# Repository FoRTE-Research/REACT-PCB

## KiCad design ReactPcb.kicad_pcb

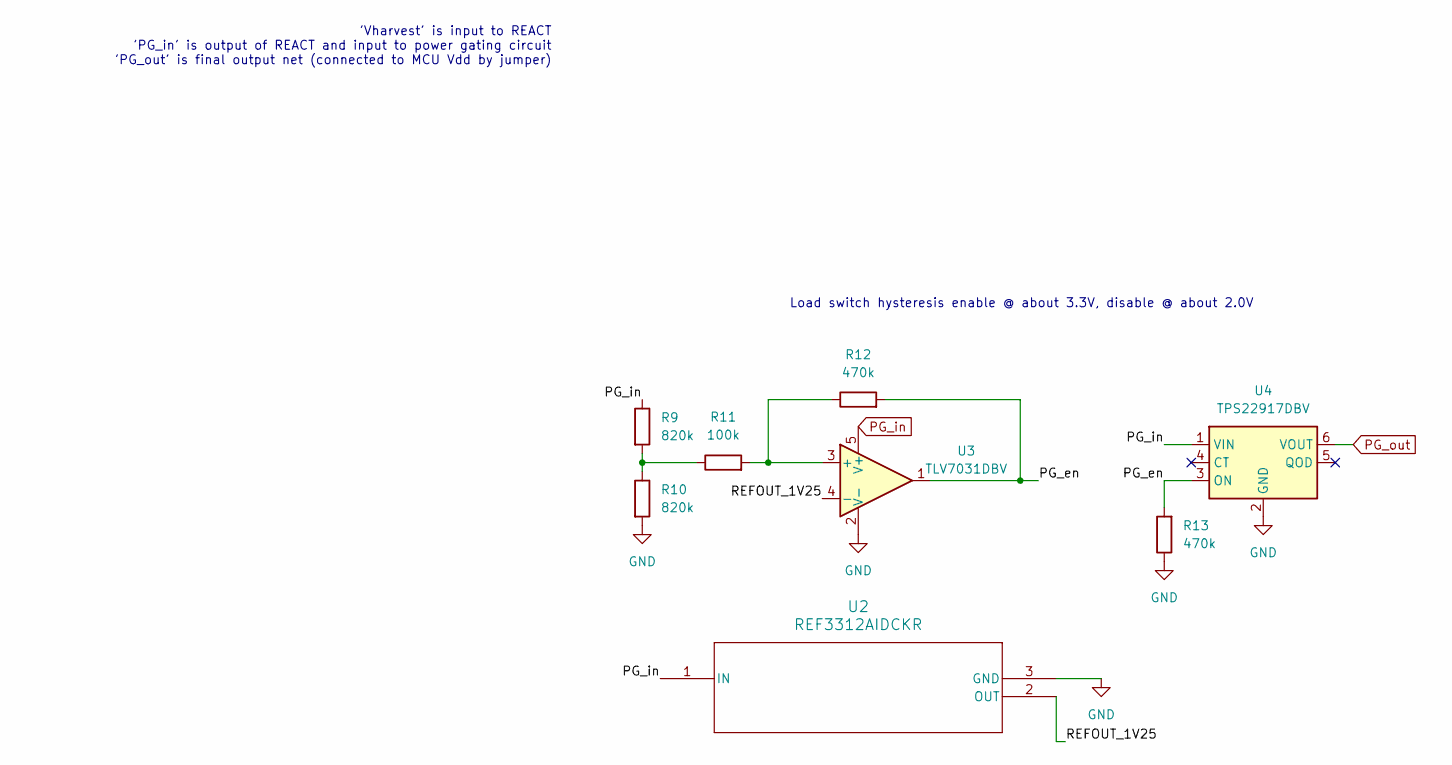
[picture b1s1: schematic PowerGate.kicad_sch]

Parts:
R9, R10: 820k; R_1206_3216Metric
R11: 100k; R_1206_3216Metric
R12, R13: 470k; R_1206_3216Metric
U2: REF3312AIDCKR; DCK3
U3: TLV7031DBV; SOT-23-5
U4: TPS22917DBV; SOT-23-6

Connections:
/Power Gate/PG_en: R12.2, R13.2, U3.1, U4.3 (ON)
/Power Gate/PG_in: R9.1, U2.1 (IN), U3.5 (V+), U4.1 (VIN)
/Power Gate/PG_out: U4.6 (VOUT)
/Power Gate/REFOUT_1V25: U2.2 (OUT), U3.4 (-)
GND: R10.2, R13.1, U2.3 (GND), U3.2 (V-), U4.2 (GND); also elsewhere on the board
unnamed: R9.2, R10.1, R11.1
unnamed: R11.2, R12.1, U3.3 (+)

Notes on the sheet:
'Vharvest' is input to REACT 'PG_in' is output of REACT and input to power gating circuit 'PG_out' is final output net (connected to MCU Vdd by jumper)
Load switch hysteresis enable @ about 3.3V, disable @ about 2.0V

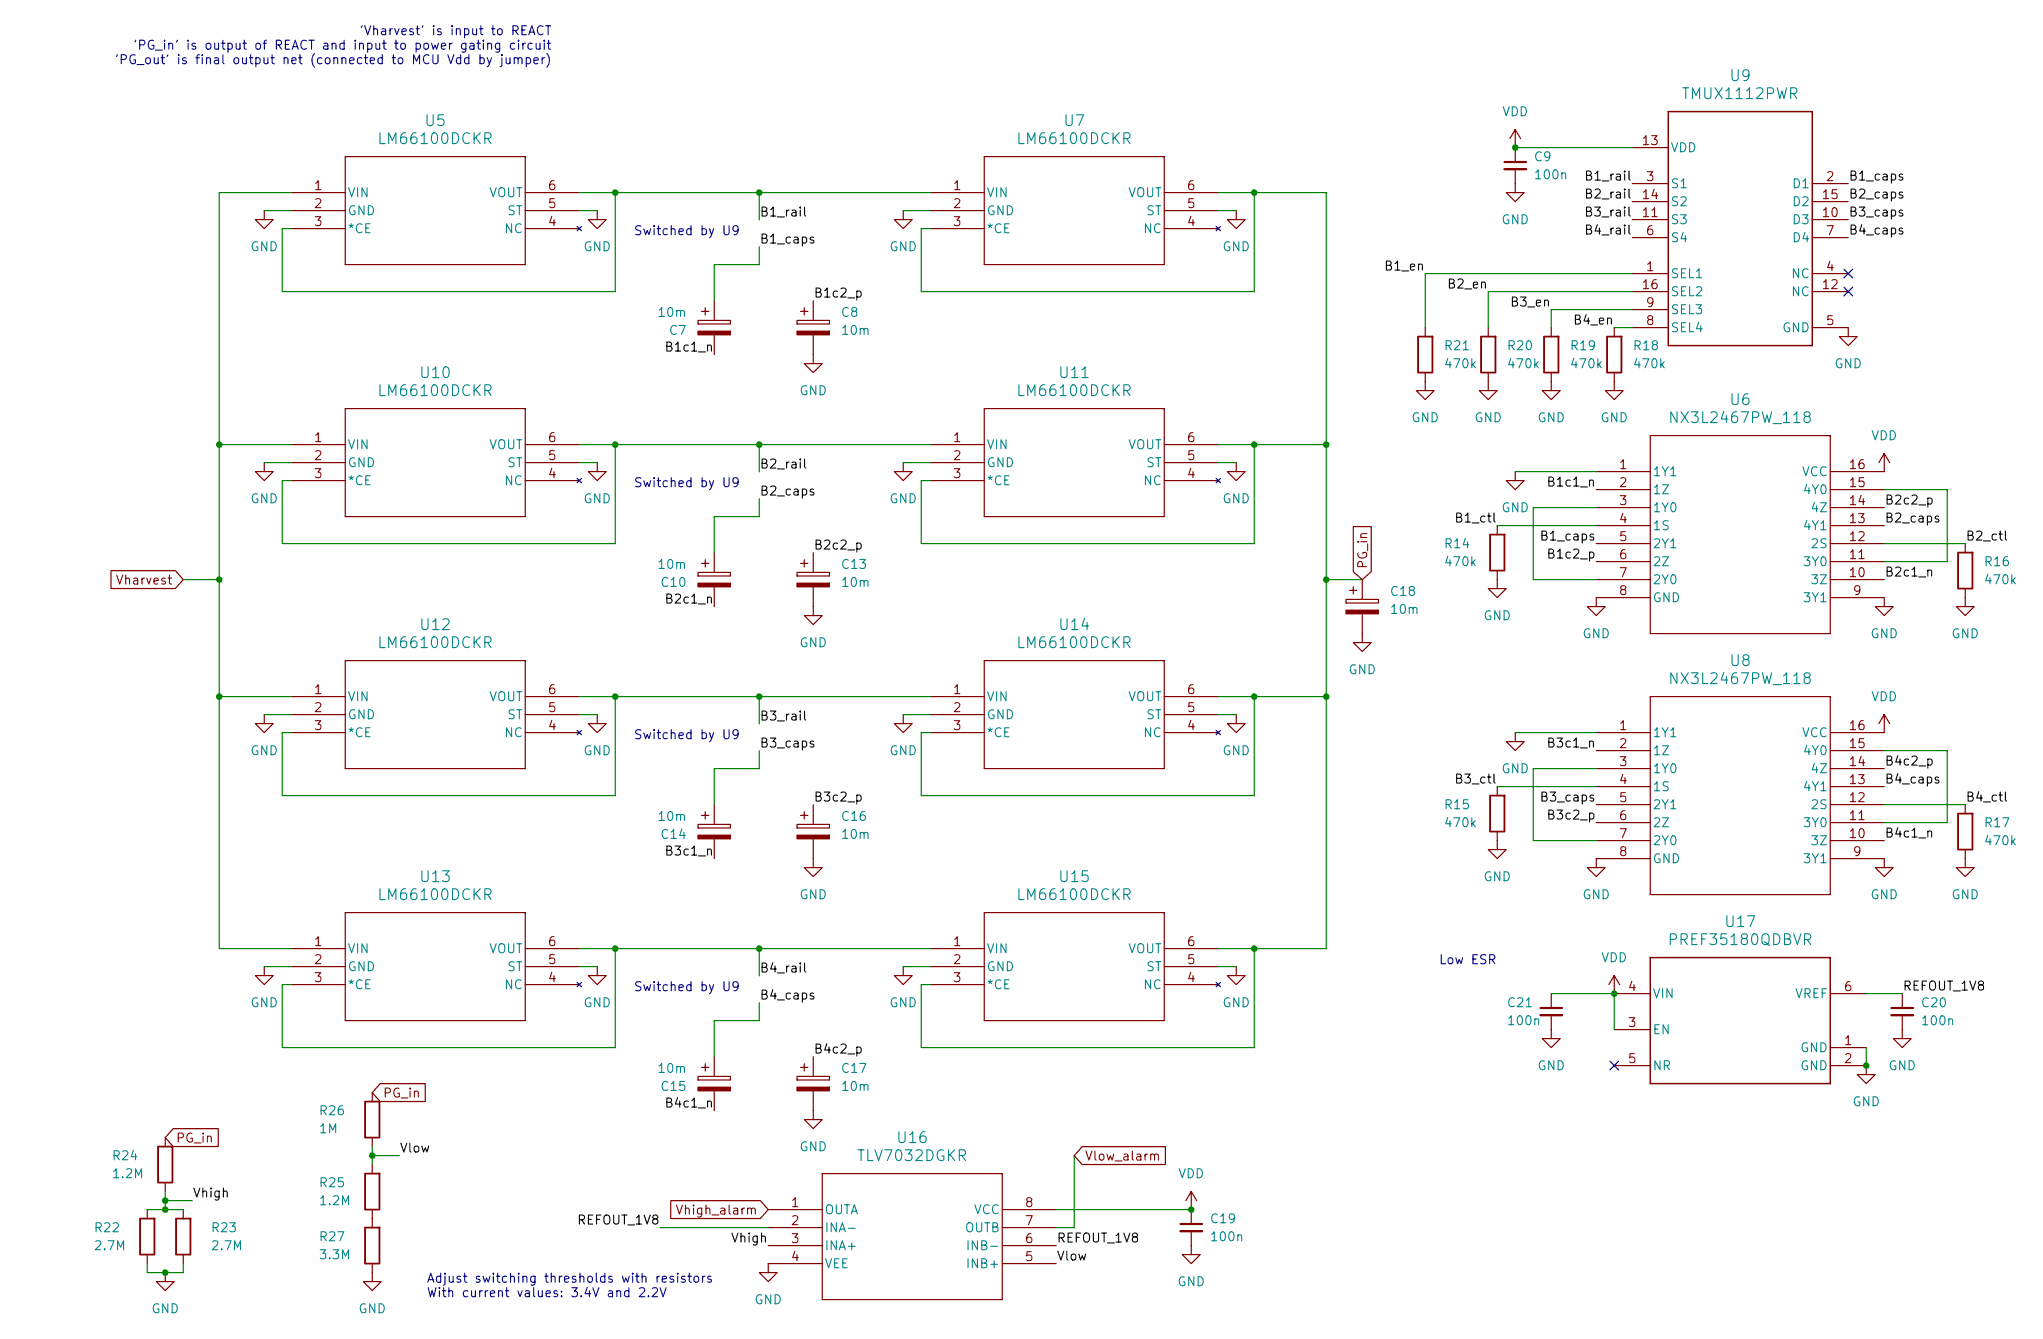
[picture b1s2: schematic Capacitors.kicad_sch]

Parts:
C7, C8, C10, C13, C14, C15, C16, C17, C18: 10m; C_Rect_L10.0mm_W5.0mm_P5.00mm_P7.50mm
C9, C19, C20, C21: 100n; C_1206_3216Metric
R14, R15, R16, R17, R18, R19, R20, R21: 470k; R_1206_3216Metric
R22, R23: 2.7M; R_1206_3216Metric
R24, R25: 1.2M; R_1206_3216Metric
R26: 1M; R_1206_3216Metric
R27: 3.3M; R_1206_3216Metric
U5, U7, U10, U11, U12, U13, U14, U15: LM66100DCKR; DCK6_TEX
U6, U8: NX3L2467PW_118; TSSOP16_SOT403-1_NXP
U9: TMUX1112PWR; PW0016A-IPC_A
U16: TLV7032DGKR; SOIC_32DGKR_TEX
U17: PREF35180QDBVR; DBV0006A-IPC_A

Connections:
/Capacitors/B1_caps: C7.1, U6.5 (2Y1), U9.2 (D1)
/Capacitors/B1_ctl: R14.2, U6.4 (1S)
/Capacitors/B1_en: R21.2, U9.1 (SEL1)
/Capacitors/B1_rail: U5.3 (*CE), U5.6 (VOUT), U7.1 (VIN), U9.3 (S1)
/Capacitors/B1c1_n: C7.2, U6.2 (1Z)
/Capacitors/B1c2_p: C8.1, U6.6 (2Z)
/Capacitors/B2_caps: C10.1, U6.13 (4Y1), U9.15 (D2)
/Capacitors/B2_ctl: R16.2, U6.12 (2S)
/Capacitors/B2_en: R20.2, U9.16 (SEL2)
/Capacitors/B2_rail: U9.14 (S2), U10.3 (*CE), U10.6 (VOUT), U11.1 (VIN)
/Capacitors/B2c1_n: C10.2, U6.10 (3Z)
/Capacitors/B2c2_p: C13.1, U6.14 (4Z)
/Capacitors/B3_caps: C14.1, U8.5 (2Y1), U9.10 (D3)
/Capacitors/B3_ctl: R15.2, U8.4 (1S)
/Capacitors/B3_en: R19.2, U9.9 (SEL3)
/Capacitors/B3_rail: U9.11 (S3), U12.3 (*CE), U12.6 (VOUT), U14.1 (VIN)
/Capacitors/B3c1_n: C14.2, U8.2 (1Z)
/Capacitors/B3c2_p: C16.1, U8.6 (2Z)
/Capacitors/B4_caps: C15.1, U8.13 (4Y1), U9.7 (D4)
/Capacitors/B4_ctl: R17.2, U8.12 (2S)
/Capacitors/B4_en: R18.2, U9.8 (SEL4)
/Capacitors/B4_rail: U9.6 (S4), U13.3 (*CE), U13.6 (VOUT), U15.1 (VIN)
/Capacitors/B4c1_n: C15.2, U8.10 (3Z)
/Capacitors/B4c2_p: C17.1, U8.14 (4Z)
/Capacitors/Pg_in: C18.1, R24.2, R26.2, U7.3 (*CE), U7.6 (VOUT), U11.3 (*CE), U11.6 (VOUT), U14.3 (*CE), U14.6 (VOUT), U15.3 (*CE), U15.6 (VOUT)
/Capacitors/REFOUT_1V8: C20.1, U16.2 (INA-), U16.6 (INB-), U17.6 (VREF)
/Capacitors/Vhigh: R22.2, R23.2, R24.1, U16.3 (INA+)
/Capacitors/Vhigh_alarm: U16.1 (OUTA)
/Capacitors/Vlow: R25.2, R26.1, U16.5 (INB+)
/Capacitors/Vlow_alarm: U16.7 (OUTB)
GND: C8.2, C9.2, C13.2, C16.2, C17.2, C18.2, C19.2, C20.2, C21.2, R14.1, R15.1, R16.1, R17.1, R18.1, R19.1, R20.1, R21.1, R22.1, R23.1, R27.1, U5.2 (GND), U5.5 (ST), U6.1 (1Y1), U6.8 (GND), U6.9 (3Y1), U7.2 (GND), U7.5 (ST), U8.1 (1Y1), U8.8 (GND), U8.9 (3Y1), U9.5 (GND), U10.2 (GND), U10.5 (ST), U11.2 (GND), U11.5 (ST), U12.2 (GND), U12.5 (ST), U13.2 (GND), U13.5 (ST), U14.2 (GND), U14.5 (ST), U15.2 (GND), U15.5 (ST), U16.4 (VEE), U17.1 (GND), U17.2 (GND); also elsewhere on the board
unnamed: R25.1, R27.2
unnamed: U6.3 (1Y0), U6.7 (2Y0)
unnamed: U6.11 (3Y0), U6.15 (4Y0)
unnamed: U8.3 (1Y0), U8.7 (2Y0)
unnamed: U8.11 (3Y0), U8.15 (4Y0)
VDD: C9.1, C19.1, C21.1, U6.16 (VCC), U8.16 (VCC), U9.13 (VDD), U16.8 (VCC), U17.3 (EN), U17.4 (VIN); also elsewhere on the board
Vharvest: U5.1 (VIN), U10.1 (VIN), U12.1 (VIN), U13.1 (VIN); also elsewhere on the board

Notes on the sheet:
Switched by U9
'Vharvest' is input to REACT 'PG_in' is output of REACT and input to power gating circuit 'PG_out' is final output net (connected to MCU Vdd by jumper)
Low ESR
Adjust switching thresholds with resistors With current values: 3.4V and 2.2V

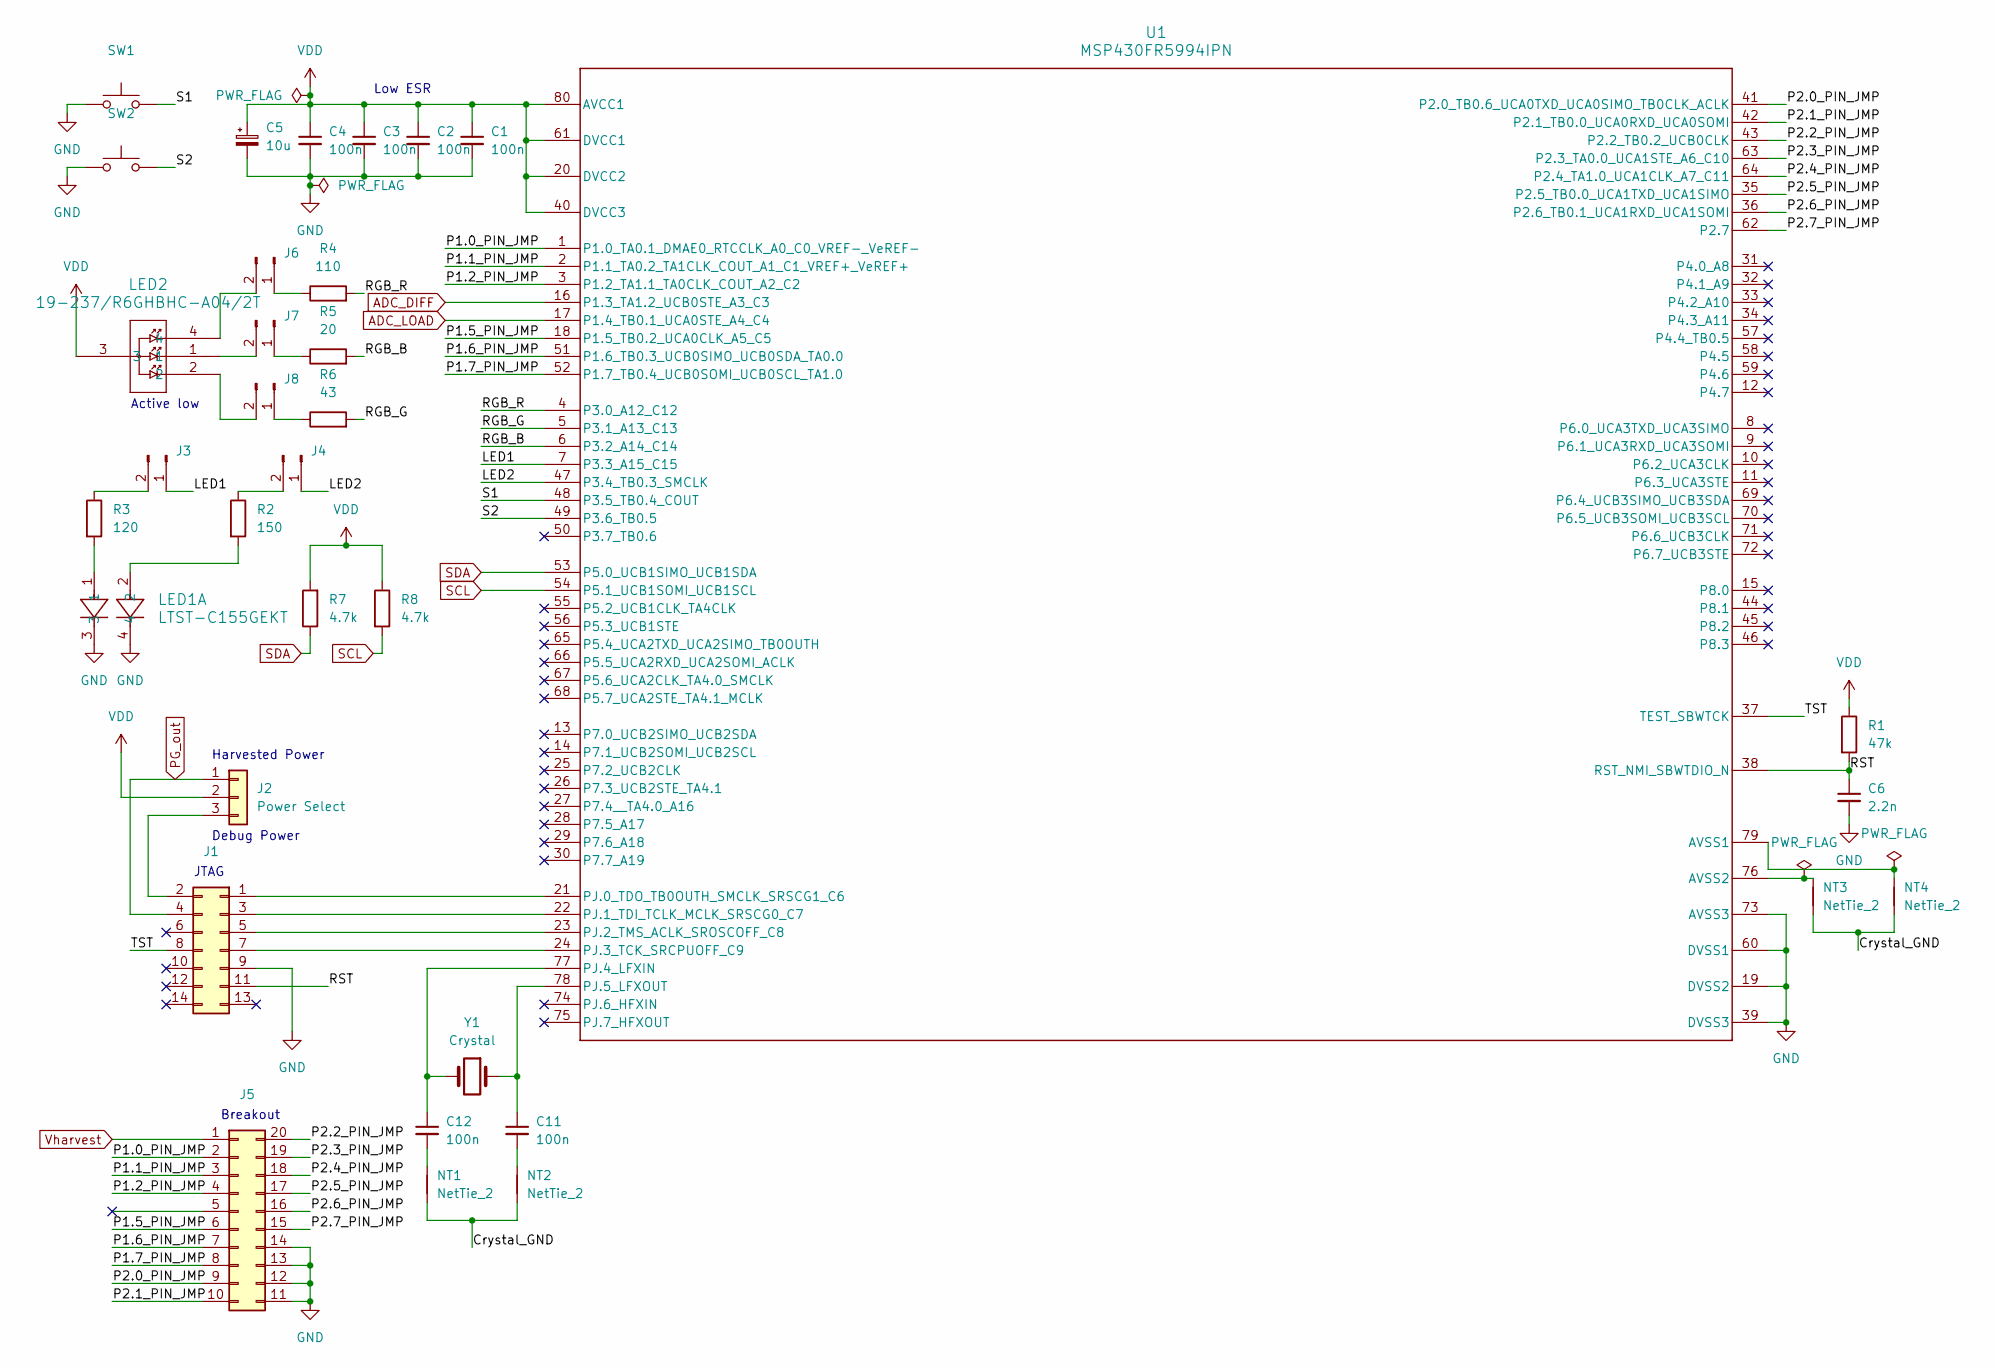
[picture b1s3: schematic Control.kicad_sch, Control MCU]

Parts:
C1, C2, C3, C4, C11, C12: 100n; C_1206_3216Metric
C5: 10u; C_1206_3216Metric
C6: 2.2n; C_1206_3216Metric
J1: Conn_02x07_Odd_Even; PinHeader_2x07_P2.54mm_Vertical
J2: Power Select; PinHeader_1x03_P2.54mm_Vertical
J3, J4, J6, J7, J8: Conn_01x02_Pin; PinHeader_1x02_P2.54mm_Vertical
J5: Conn_02x10_Counter_Clockwise; PinHeader_2x10_P2.54mm_Vertical
LED1: LTST-C155GEKT; DIODE_LTST-C155GEKT_LTO
LED2: 19-237/R6GHBHC-A04/2T; EAST1616RGB_SMD_B_EVE
NT1, NT2, NT3, NT4: NetTie_2; NetTie-2_SMD_Pad0.2mm
R1: 47k; R_1206_3216Metric
R2: 150; R_1206_3216Metric
R3: 120; R_1206_3216Metric
R4: 110; R_1206_3216Metric
R5: 20; R_1206_3216Metric
R6: 43; R_1206_3216Metric
R7, R8: 4.7k; R_1206_3216Metric
SW1, SW2: SW_Push; SW_TL59NF160Q
U1: MSP430FR5994IPN; PN0080A_N
Y1: Crystal; XTAL_MS1V-T1K-32.768KHZ-12.5PF-20PPM-TA-QC

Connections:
/Control/Crystal_GND: NT1.1, NT2.1, NT3.1, NT4.1
/Control/LED1: J3.1, U1.7 (P3.3_A15_C15)
/Control/LED2: J4.1, U1.47 (P3.4_TB0.3_SMCLK)
/Control/P1.0_PIN_JMP: J5.2, U1.1 (P1.0_TA0.1_DMAE0_RTCCLK_A0_C0_VREF-_VeR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)
/Control/P1.1_PIN_JMP: J5.3, U1.2 (P1.1_TA0.2_TA1CLK_COUT_A1_C1_VREF+_VeRE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)
/Control/P1.2_PIN_JMP: J5.4, U1.3 (P1.2_TA1.1_TA0CLK_COUT_A2_C2)
/Control/P1.5_PIN_JMP: J5.6, U1.18 (P1.5_TB0.2_UCA0CLK_A5_C5)
/Control/P1.6_PIN_JMP: J5.7, U1.51 (P1.6_TB0.3_UCB0SIMO_UCB0SDA_TA0.0)
/Control/P1.7_PIN_JMP: J5.8, U1.52 (P1.7_TB0.4_UCB0SOMI_UCB0SCL_TA1.0)
/Control/P2.0_PIN_JMP: J5.9, U1.41 (P2.0_TB0.6_UCA0TXD_UCA0SIMO_TB0CLK_ACLK)
/Control/P2.1_PIN_JMP: J5.10, U1.42 (P2.1_TB0.0_UCA0RXD_UCA0SOMI)
/Control/P2.2_PIN_JMP: J5.20, U1.43 (P2.2_TB0.2_UCB0CLK)
/Control/P2.3_PIN_JMP: J5.19, U1.63 (P2.3_TA0.0_UCA1STE_A6_C10)
/Control/P2.4_PIN_JMP: J5.18, U1.64 (P2.4_TA1.0_UCA1CLK_A7_C11)
/Control/P2.5_PIN_JMP: J5.17, U1.35 (P2.5_TB0.0_UCA1TXD_UCA1SIMO)
/Control/P2.6_PIN_JMP: J5.16, U1.36 (P2.6_TB0.1_UCA1RXD_UCA1SOMI)
/Control/P2.7_PIN_JMP: J5.15, U1.62 (P2.7)
/Control/PG_out: J1.4, J2.1
/Control/RGB_B: R5.2, U1.6 (P3.2_A14_C14)
/Control/RGB_G: R6.2, U1.5 (P3.1_A13_C13)
/Control/RGB_R: R4.2, U1.4 (P3.0_A12_C12)
/Control/RST: C6.1, J1.11, R1.2, U1.38 (RST_NMI_SBWTDIO_N)
/Control/S1: SW1.2, U1.48 (P3.5_TB0.4_COUT)
/Control/S2: SW2.2, U1.49 (P3.6_TB0.5)
/Control/TST: J1.8, U1.37 (TEST_SBWTCK)
ADC_DIFF: U1.16 (P1.3_TA1.2_UCB0STE_A3_C3)
ADC_LOAD: U1.17 (P1.4_TB0.1_UCA0STE_A4_C4)
GND: C1.2, C2.2, C3.2, C4.2, C5.2, C6.2, J1.9, J5.11, J5.12, J5.13, J5.14, LED1.3, LED1.4, SW1.1, SW2.1, U1.19 (DVSS2), U1.39 (DVSS3), U1.60 (DVSS1), U1.73 (AVSS3); also elsewhere on the board
unnamed: C11.2, NT2.2
unnamed: C12.2, NT1.2
unnamed: J1.1, U1.21 (PJ.0_TDO_TB0OUTH_SMCLK_SRSCG1_C6)
unnamed: J1.2, J2.3
unnamed: J1.3, U1.22 (PJ.1_TDI_TCLK_MCLK_SRSCG0_C7)
unnamed: J1.5, U1.23 (PJ.2_TMS_ACLK_SROSCOFF_C8)
unnamed: J1.7, U1.24 (PJ.3_TCK_SRCPUOFF_C9)
unnamed: J3.2, R3.1
unnamed: J4.2, R2.1
unnamed: J6.1, R4.1
unnamed: J6.2, LED2.4
unnamed: J7.1, R5.1
unnamed: J7.2, LED2.1
unnamed: J8.1, R6.1
unnamed: J8.2, LED2.2
unnamed: LED1.1, R3.2
unnamed: LED1.2, R2.2
unnamed: NT4.2, U1.79 (AVSS1)
unnamed: NT3.2, U1.76 (AVSS2)
unnamed: C12.1, U1.77 (PJ.4_LFXIN), Y1.2
unnamed: C11.1, U1.78 (PJ.5_LFXOUT), Y1.1
SCL: R8.2, U1.54 (P5.1_UCB1SOMI_UCB1SCL)
SDA: R7.1, U1.53 (P5.0_UCB1SIMO_UCB1SDA)
VDD: C1.1, C2.1, C3.1, C4.1, C5.1, J2.2, LED2.3, R1.1, R7.2, R8.1, U1.20 (DVCC2), U1.40 (DVCC3), U1.61 (DVCC1), U1.80 (AVCC1); also elsewhere on the board
Vharvest: J5.1; also elsewhere on the board

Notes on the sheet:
JTAG
Debug Power
Active low
Breakout
Low ESR
Harvested Power

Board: 2 copper layers, 82 parts (0 on the bottom side), 89 nets, no tracks yet.

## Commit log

2024-12-20 Sch upload
2025-05-02 Upload 1.0 code
